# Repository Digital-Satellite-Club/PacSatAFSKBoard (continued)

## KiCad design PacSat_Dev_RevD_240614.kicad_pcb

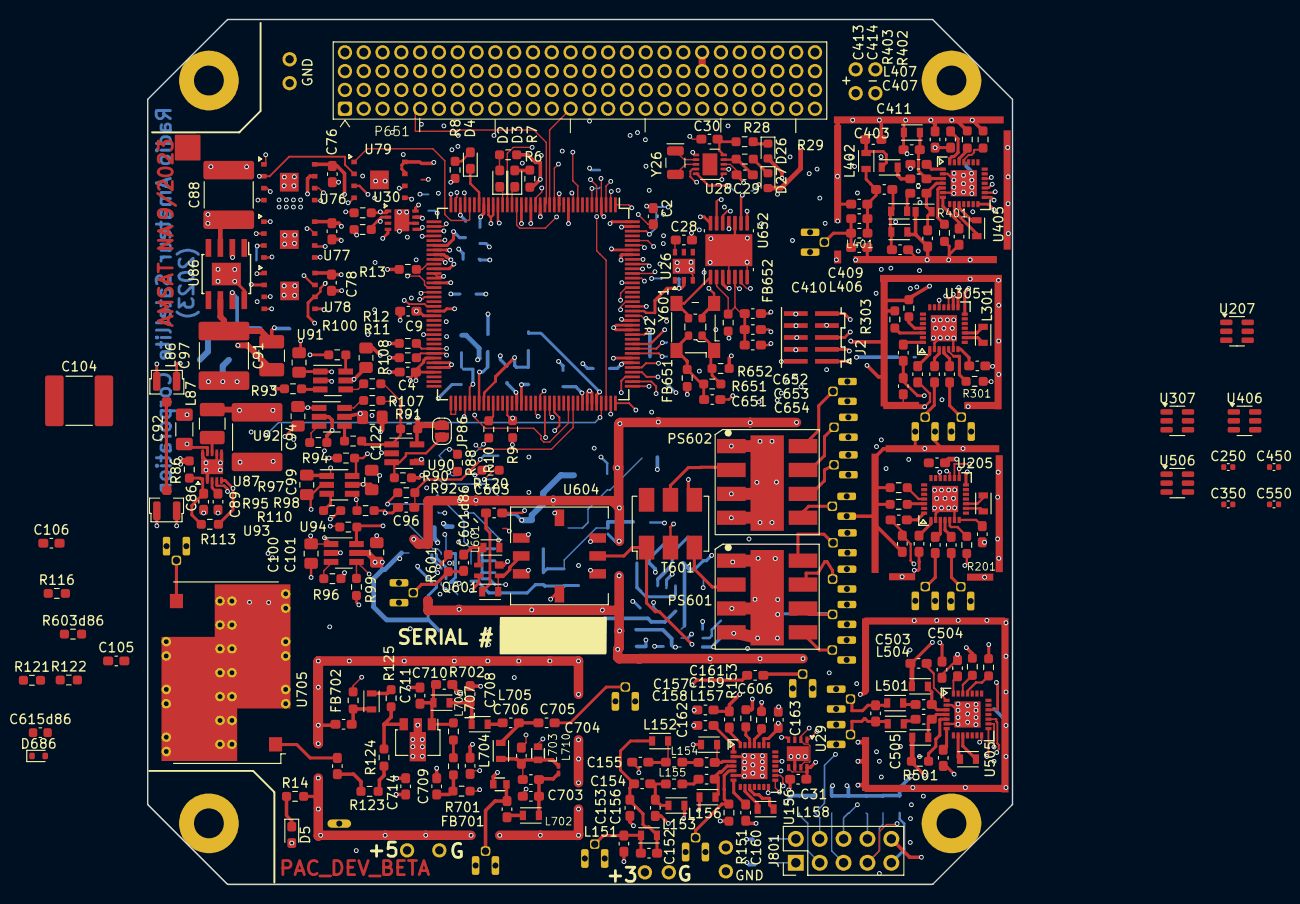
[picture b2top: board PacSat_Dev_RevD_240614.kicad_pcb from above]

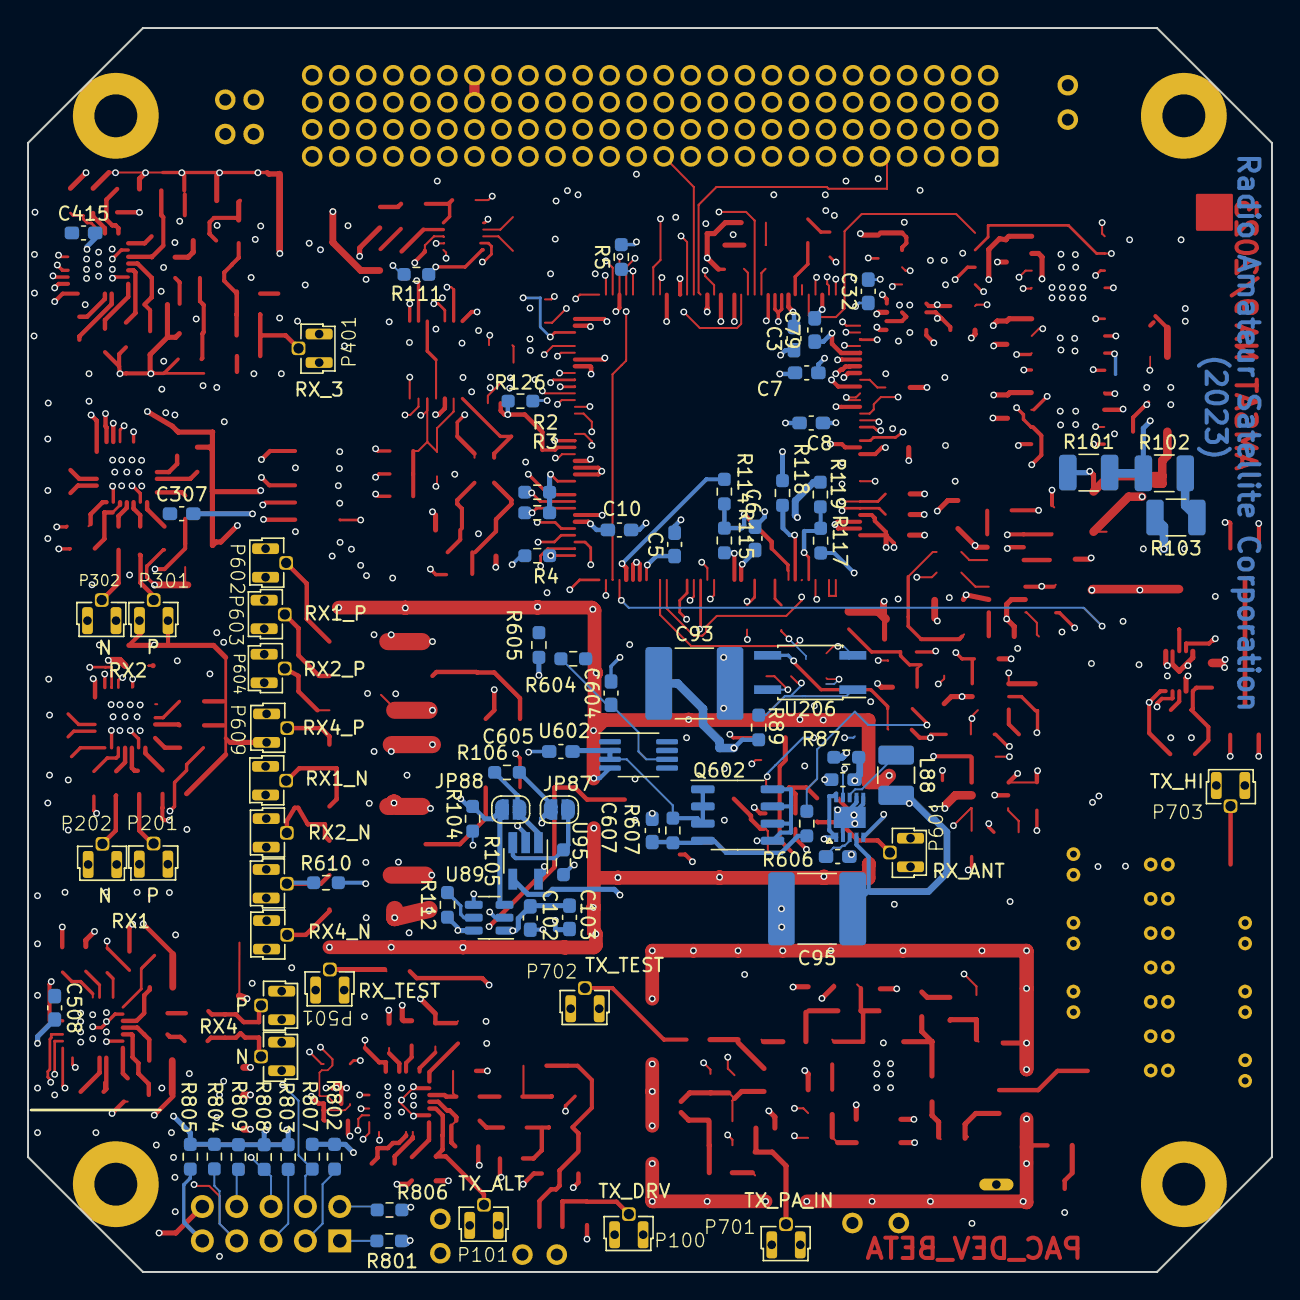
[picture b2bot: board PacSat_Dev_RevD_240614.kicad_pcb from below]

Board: 6 copper layers, 92.0 x 92.0 mm, 354 parts (85 on the bottom side), 245 nets.

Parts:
C2, C3, C4, C5, C6, C7, C8, C9, C10, C31, C32, C76, C77, C78, C79: 100n; C_0603_1608Metric_Pad1.08x0.95mm_HandSolder
C28, C86, C87: 470n; C_0603_1608Metric_Pad1.08x0.95mm_HandSolder
C29, C30: 22u; C_0603_1608Metric_Pad1.08x0.95mm_HandSolder
C88: 16V; C_2220_5750Metric_Pad1.97x5.40mm_HandSolder
C89, C90: 1000p; C_0603_1608Metric_Pad1.08x0.95mm_HandSolder
C91: 22u 10V; C_2220_5750Metric_Pad1.97x5.40mm_HandSolder
C92: 10u; C_1206_3216Metric_Pad1.33x1.80mm_HandSolder
C93: 10u; C_2220_5750Metric_Pad1.97x5.40mm_HandSolder
C94, C95: 22u; C_2220_5750Metric_Pad1.97x5.40mm_HandSolder
C96, C714: 10u; C_0603_1608Metric_Pad1.08x0.95mm_HandSolder
C97, C98, C99, C100, C101, C121, C122, C123: 1u; C_0805_2012Metric_Pad1.18x1.45mm_HandSolder
C102, C103, C159, C160, C163, C203, C204, C207, C303, C304, C307, C411, C412, C415, C504, C505, C508: 10n; C_0603_1608Metric_Pad1.08x0.95mm_HandSolder
C104: 10u 10v; C_2220_5750Metric_Pad1.97x5.40mm_HandSolder
C105, C106, C603, C607: 0.1 u; C_0603_1608Metric_Pad1.08x0.95mm_HandSolder
C151, C152, C153, C402, C704: NS; C_0603_1608Metric_Pad1.08x0.95mm_HandSolder
C154: 5p1; C_0603_1608Metric_Pad1.08x0.95mm_HandSolder
C155: 11p; C_0603_1608Metric_Pad1.08x0.95mm_HandSolder
C156, C406, C702: 5p6; C_0603_1608Metric_Pad1.08x0.95mm_HandSolder
C157, C158, C201, C202, C301, C302, C409, C410, C501, C701, C703: 4p3; C_0603_1608Metric_Pad1.08x0.95mm_HandSolder
C161, C205, C305, C413, C506: 6.8p; C_0603_1608Metric_Pad1.08x0.95mm_HandSolder
C162, C206, C306, C407, C408, C414, C507: 10p; C_0603_1608Metric_Pad1.08x0.95mm_HandSolder
C250, C350, C450, C550: .1u; C_0402_1005Metric
C401, C403: 27p; C_0603_1608Metric_Pad1.08x0.95mm_HandSolder
C404: 12p; C_0603_1608Metric_Pad1.08x0.95mm_HandSolder
C405: 1p; C_0603_1608Metric_Pad1.08x0.95mm_HandSolder
C502, C503: 22p; C_0603_1608Metric_Pad1.08x0.95mm_HandSolder
C601d86: 6p; C_0603_1608Metric_Pad1.08x0.95mm_HandSolder
C604, C605, C707: 1u; C_0603_1608Metric_Pad1.08x0.95mm_HandSolder
C606: 1n; C_0603_1608Metric_Pad1.08x0.95mm_HandSolder
C615d86: 10u; C_0603_1608Metric
C651, C652, C653, C654: 0.1u; C_0603_1608Metric_Pad1.08x0.95mm_HandSolder
C705, C717: 2200p; C_0603_1608Metric_Pad1.08x0.95mm_HandSolder
C706: 18p; C_0603_1608Metric_Pad1.08x0.95mm_HandSolder
C708, C711: 15p; C_0603_1608Metric_Pad1.08x0.95mm_HandSolder
C709, C712: 100p; C_0603_1608Metric_Pad1.08x0.95mm_HandSolder
C710: 56p; C_0603_1608Metric_Pad1.08x0.95mm_HandSolder
D2: RED; LED_0603_1608Metric_Pad1.05x0.95mm_HandSolder
D3: YEL; LED_0603_1608Metric_Pad1.05x0.95mm_HandSolder
D4: GRN; LED_0603_1608Metric_Pad1.05x0.95mm_HandSolder
D5: LED; LED_0603_1608Metric_Pad1.05x0.95mm_HandSolder
D26, D27: RB521CS30L,315; D_0603_1608Metric
D686: BZX58550-C1V8-QX; D_SOD-523
FB651, FB652: FerriteBead_Small; R_0603_1608Metric_Pad0.98x0.95mm_HandSolder
FB701, FB702: 2743019447; R_0603_1608Metric_Pad0.98x0.95mm_HandSolder
H10, H11, H12, H13, H14, H15, H16, H17, H18, H19, H20, H21: Wire_Hole
H101, H102, H103, H104: CUBESAT_MOUNT_HOLE
J2: CONN_02X05; FTSH-105-01-L-DV-K
J801: Conn_02x05_Odd_Even; PinHeader_2x05_P2.54mm_Vertical
JP86, JP87: Disable Watchdog; SolderJumper-2_P1.3mm_Open_RoundedPad1.0x1.5mm
JP88: Disable WD Shutdown; SolderJumper-2_P1.3mm_Open_RoundedPad1.0x1.5mm
L86, L87, L88: 3u3; L_1210_3225Metric_Pad1.42x2.65mm_HandSolder
L151, L158, L201, L301, L408, L505: 0; L_Murata_LQH2MCNxxxx02_2.0x1.6mm
L152, L153: 27n; L_Murata_LQH2MCNxxxx02_2.0x1.6mm
L154, L155: 43n; L_0603_1608Metric_Pad1.05x0.95mm_HandSolder
L156, L157: 100n; L_Murata_LQH2MCNxxxx02_2.0x1.6mm
L401: 30nh; L_0603_1608Metric_Pad1.05x0.95mm_HandSolder
L402, L403, L501, L502, L503, L504: 68n; L_Murata_LQH2MCNxxxx02_2.0x1.6mm
L404, L405: 120n; L_Murata_LQH2MCNxxxx02_2.0x1.6mm
L406, L407: 150n; L_Murata_LQH2MCNxxxx02_2.0x1.6mm
L601: 620nH; L_Murata_LQH2MCNxxxx02_2.0x1.6mm
L602: 120 nH; L_Murata_LQH2MCNxxxx02_2.0x1.6mm
L701: 100n; L_0603
L702: 43n; L_Murata_LQH2MCNxxxx02_2.0x1.6mm
L703: 18n; L_0603
L704: 1n2; L_Murata_LQH2MCNxxxx02_2.0x1.6mm
L705, L706: 5n5; L_Murata_LQH2MCNxxxx02_2.0x1.6mm
L707: 16n6; L_Murata_LQH2MCNxxxx02_2.0x1.6mm
L710: 4n7; L_0201_0603Metric_Pad0.64x0.40mm_HandSolder
P100, P201, P202, P301, P302, P401, P501, P502, P602, P603, P604, P605, P606, P607, P608, P609, P610, P701: U_FL
P101, P601, P702, P703: U_FL
P651: Conn_04x26_Pin; PacSat_Dev_4_26
PS601, PS602: AD4PS+1; CJ725
Q601: SAV-331+; TB-471
Q602: SO-8_3.9x4.9mm_P1.27mm
Q701: ATF05MS004NT1; SOT-89-3
R2, R3, R4, R5, R13: 3k3; R_0603_1608Metric_Pad0.98x0.95mm_HandSolder
R6, R7, R8, R604: 3K; R_0603_1608Metric_Pad0.98x0.95mm_HandSolder
R9, R10, R11, R12: 1k; R_0603_1608Metric_Pad0.98x0.95mm_HandSolder
R14: 2.4K; R_0603_1608Metric_Pad0.98x0.95mm_HandSolder
R28, R29, R30, R31, R104, R111: 4k7; R_0603_1608Metric_Pad0.98x0.95mm_HandSolder
R86, R87, R108, R109, R152, R153, R202, R203, R302, R303, R402, R403, R502, R503: 0R; R_0603_1608Metric_Pad0.98x0.95mm_HandSolder
R88: 20; R_0603_1608Metric_Pad0.98x0.95mm_HandSolder
R89: 2 1/4 W; R_0603_1608Metric_Pad0.98x0.95mm_HandSolder
R90, R91, R105, R106: 10k; R_0603_1608Metric_Pad0.98x0.95mm_HandSolder
R92: 1K; R_0603_1608Metric_Pad0.98x0.95mm_HandSolder
R93, R94, R96: 45k8 1%; R_0603_1608Metric_Pad0.98x0.95mm_HandSolder
R95: 143k 1%; R_0603_1608Metric_Pad0.98x0.95mm_HandSolder
R97, R98, R99, R100, R107, R110, R112, R114, R115, R117, R118, R119, R651, R652, R801, R802, R803, R804, R805, R806, R807, R808, R809: 10K; R_0603_1608Metric_Pad0.98x0.95mm_HandSolder
R101: PLTT1206Z2743BGTS; R_1210_3225Metric_Pad1.30x2.65mm_HandSolder
R102: PLTT1206Z0303BGTS; R_1210_3225Metric_Pad1.30x2.65mm_HandSolder
R103: PLTT1206Z0011BGTS; R_1210_3225Metric_Pad1.30x2.65mm_HandSolder
R113: 3.8K; R_0603_1608Metric_Pad0.98x0.95mm_HandSolder
R116: 440K; R_0603_1608Metric_Pad0.98x0.95mm_HandSolder
R120: 10 1/2 W; R_0603_1608Metric_Pad0.98x0.95mm_HandSolder
R121: 580K; R_0603_1608Metric_Pad0.98x0.95mm_HandSolder
R122: 420K; R_0603_1608Metric_Pad0.98x0.95mm_HandSolder
R123, R124, R702: 0; R_0603_1608Metric_Pad0.98x0.95mm_HandSolder
R125, R151, R201, R301, R401, R501, R610, R701: 50; R_0603_1608Metric_Pad0.98x0.95mm_HandSolder
R126: 20K; R_0603_1608Metric_Pad0.98x0.95mm_HandSolder
R601: 500K; R_0603_1608Metric_Pad0.98x0.95mm_HandSolder
R603d86: 27 1/2 Watt; R_0603_1608Metric_Pad0.98x0.95mm_HandSolder
R605: 2K; R_0603_1608Metric_Pad0.98x0.95mm_HandSolder
R606: 47K; R_0603_1608Metric_Pad0.98x0.95mm_HandSolder
R607: 1MEG; R_0603_1608Metric_Pad0.98x0.95mm_HandSolder
T601: ADT4-1WT+; Mini-Circuits_CD542_H2.84mm
TP1, TP2: U_FL; U_FL SMD
U2: TMS570LS0914PGE; TQFP-144_20x20mm_Pitch0.5mm
U26: DS28E83Q+T; TDFN_T633_2
U28: MAX31331TETB+; TDFN-10-1EP_3x3mm_P0.5mm_EP0.9x2mm
U29, U30: MAX31725MTA+; TDFN_T833_2
U76, U77, U78, U79: MR25H40CDE; MR2xH40_DFN_SmallFlag
U86: TPS7A7001DDA; TI_SO-PowerPAD-8
U87: MAX1556AEBT+; TDFN_T1033_1
U88: MAX1556A; TDFN_T1033_1
U89: TPS22917DBV; SOT-23-6
U90, U95: STWD100NYWY3F; SOT-23-5_HandSoldering
U91, U92, U93, U94: MAX4995ALAUT; SOT-23-6_Handsoldering
U156, U205, U305, U405, U505: AX5043; QFN28
U201: RFShield_OnePiece; RF_SHIELD_BMI_S_201_F_U201
U206: TLP3905; SO-4_4.4x3.6mm_P2.54mm
U207, U307, U406, U506: TPS22929D; SOT-23-6
U301: RFShield_OnePiece; RF_SHIELD_BMI_S_201_F_U301
U401: RFShield_OnePiece; RF_SHIELD_BMI_S_202_F_U401
U501: RFShield_OnePiece; RF_SHIELD_BMI_S_202_F_U501
U602: LT6657AHMS8-2.5; MSOP-8_3x3mm_P0.65mm
U604: RBP-140+; Mini-Circuits_GP731
U652: CDCLVC1106; HTSSOP-14-1EP_4.4x5mm_P0.65mm_EP3.4x5mm_Mask3x3.1mm
U701: RFShield_OnePiece; RF_SHIELD_PAD
U705: SXBP-425+; Mini-Circuits_HF1139_LandPatternPL-230
Y26: 32.768kHz; Crystal_SMD_EuroQuartz_EQ161-2Pin_3.2x1.5mm
Y601: 588S160X2CAT; Oscillator_SMD_CTS_4X5mm
Y602: ECS-TXO-2016-33-160-TR; Oscillator_SMD_ECS_2520MV-xxx-xx-4Pin_2.5x2.0mm

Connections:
+1V2: C3.1, C5.1, C6.1, C9.1, C10.1, C97.1, R118.1, U2.17 (VCC), U2.29 (VCC), U2.45 (VCC), U2.48 (VCC), U2.49 (VCC), U2.57 (VCC), U2.87 (VCC), U2.101 (VCC), U2.114 (VCC), U2.123 (VCC), U2.137 (VCC), U2.143 (VCC), U91.1 (OUT)
+3.3V: C2.1, C4.1, C7.1, C8.1, C32.1, C76.1, C77.1, C78.1, C79.1, C98.1, C605.1, D26.2 (A), FB651.1, FB652.1, H12.1, J2.1, P651.1, P651.9, Q602.1 (S), Q602.2 (S), Q602.3 (S), R2.1, R3.1, R4.1, R6.1, R7.1, R8.1, R11.1, R13.1, R30.1, R31.1, R97.1, R99.1, R100.1, R104.1, R107.1, R110.1, R114.1, R126.1, R607.2, R801.1, R802.1, R803.1, R804.1, R805.1, R806.1, R807.1, R808.1, R809.1, U2.10 (VCCIO), U2.26 (VCCIO), U2.42 (VCCIO), U2.66 (ADREFHI), U2.69 (VCCAD), U2.104 (VCCIO), U2.120 (VCCIO), U2.134 (VCCP), U2.136 (VCCIO), U30.5 (A2), U30.8 (VDD), U76.3 (WP_N), U76.7 (HOLD_N), U76.8 (VDD), U77.3 (WP_N), U77.7 (HOLD_N), U77.8 (VDD), U78.3 (WP_N), U78.7 (HOLD_N), U78.8 (VDD), U79.3 (WP_N), U79.7 (HOLD_N), U79.8 (VDD), U92.1 (OUT), U602.2 (Vin), U602.3 (~SHDN)
+5V: C707.1, C714.1, D5.2 (A), FB702.1, H14.1
-7V BIAS: R92.2, R116.2, R606.1
/RX_1_ax5044/RX1_N: C202.2, P202.1 (In)
/RX_1_ax5044/RX1_P: C201.2, P201.1 (In)
/RX_1_ax5044/RXANT_N: C202.1, U205.4 (ANTN)
/RX_1_ax5044/RXANT_P: C201.1, U205.3 (ANTP)
/RX_2_ax5045/RX2ANT_N: C302.1, U305.4 (ANTN)
/RX_2_ax5045/RX2ANT_P: C301.1, U305.3 (ANTP)
/RX_2_ax5045/RX2A_N: C302.2, P302.1 (In)
/RX_2_ax5045/RX2a_P: C301.2, P301.1 (In)
/RX_3_ax5045/RX3_N: C408.1, C410.1, L406.2, U405.4 (ANTN)
/RX_3_ax5045/RX3_P: C407.1, C409.1, L407.2, U405.3 (ANTP)
/RX_3_ax5045/RX3a_N: C410.2, L405.2
/RX_3_ax5045/RX3a_P: C409.2, L404.2
/RX_3_ax5045/RX3b_N: C404.1, C406.1, L403.1, L405.1
/RX_3_ax5045/RX3b_P: C405.1, L402.2, L404.1
/RX_4_ax5045/RX4ANT_N: C503.1, L504.2, U505.4 (ANTN)
/RX_4_ax5045/RX4ANT_P: C502.1, L503.1, U505.3 (ANTP)
/RX_4_ax5045/RX4a_N: C503.2, L502.2
/RX_4_ax5045/RX4a_P: C502.2, L501.2
/RX_4_ax5045/RX4b_N: C501.2, L502.1, P502.1 (In)
/RX_4_ax5045/RX4b_P: C501.1, L501.1, P501.1 (In)
/Rx_Power_Divider/Port1_N: P605.1 (In), PS601.8 (Port1)
/Rx_Power_Divider/Port1_P: P602.1 (In), PS602.8 (Port1)
/Rx_Power_Divider/Port2_N: P606.1 (In), PS601.7 (Port2)
/Rx_Power_Divider/Port2_P: P603.1 (In), PS602.7 (Port2)
/Rx_Power_Divider/Port3_N: P607.1 (In), PS601.6 (Port3), R610.1
/Rx_Power_Divider/Port3_P: P604.1 (In), PS602.6 (Port3)
/Rx_Power_Divider/Port4_N: P608.1 (In), PS601.5 (Port4)
/Rx_Power_Divider/Port4_P: P609.1 (In), PS602.5 (Port4)
/Rx_Power_Divider/S+: PS602.2 (S1), T601.5 (SB)
/Rx_Power_Divider/S-: PS601.2 (S1), T601.3 (SA)
/TX_ax5043/TCANT_N: C158.1, L156.2, U156.4 (ANTN)
/TX_ax5043/TXANT_P: C157.1, L157.2, U156.3 (ANTP)
/TX_ax5043/TXa_N: C158.2, L155.2
/TX_ax5043/TXa_P: C157.2, L154.2
/TX_ax5043/TXb_N: C154.1, C156.1, L153.1, L155.1
/TX_ax5043/TXb_P: C155.1, L152.2, L154.1
ALERT_SIGNAL: P651.49, U2.15 (N2HET1_22)
ATTACHED: P651.31, U2.106 (N2HET1_8)
AX5043 PWR CTL: R98.1, U2.99 (MIBSPI5SIMO_0), U93.4 (ON)
AX5043_3V3: C31.1, C99.1, C102.2, C103.1, C250.1, C350.1, C450.1, C550.1, U29.5 (A2), U29.8 (VDD), U89.1 (VIN), U93.1 (OUT), U207.4 (VIN), U207.6 (VIN), U307.4 (VIN), U307.6 (VIN), U406.4 (VIN), U406.6 (VIN), U506.4 (VIN), U506.6 (VIN)
AX5043_CLK: J801.8, R809.2, U2.53 (MIBSPI3CLK), U156.15 (CLK), U205.15 (CLK), U305.15 (CLK), U405.15 (CLK), U505.15 (CLK)
AX5043_IRQ: J801.2, R806.2
AX5043_IRQ_RX1: U2.5 (GIOA_1), U205.19 (IRQ)
AX5043_IRQ_RX2: U2.126 (GOIB_0), U305.19 (IRQ)
AX5043_IRQ_RX3: U2.22 (GIOA_7), U405.19 (IRQ)
AX5043_IRQ_RX4: U2.14 (GIOA_5), U505.19 (IRQ)
AX5043_IRQ_TX: U2.142 (GIOB_2), U156.19 (IRQ)
AX5043_MISO: J801.6, R808.2, U2.51 (MIBSPI3SOMI), U156.16 (MISO), U205.16 (MISO), U305.16 (MISO), U405.16 (MISO), U505.16 (MISO)
AX5043_MOSI: J801.4, R807.2, U2.52 (MIBSPI3SIMO), U156.17 (MOSI), U205.17 (MOSI), U305.17 (MOSI), U405.17 (MOSI), U505.17 (MOSI)
AX5043_SEL1: J801.3, R802.2, U2.24 (N2HET1_3), U205.14 (SEL)
AX5043_SEL2: J801.5, R803.2, U2.33 (N2HET1_7), U305.14 (SEL)
AX5043_SEL3: J801.7, R804.2, U2.35 (N2HET1_9), U405.14 (SEL)
AX5043_SEL4: J801.9, R805.2, U2.36 (N2HET1_4), U505.14 (SEL)
AX5043_SEL_TX: J801.1, R801.2, U2.124 (N2HET1_12), U156.14 (SEL)
Alarm XMIT Shutdown: JP88.1, R104.2, U2.118 (N2HET1_10), U28.4 (INTA_N), U89.3 (ON)
CMD_MODE: P651.27, U2.127 (N2HET1_30)
CURRENT_FAULT_U89: U2.73 (AD1IN_2), U2.74 (AD1IN_3)
Clock0: C161.2, C162.1, U652.3 (YO)
Clock1: C205.1, C206.1, U652.14 (Y1)
Clock2: C305.1, C306.1, U652.11 (Y2)
Clock3: C413.1, C414.1, U652.13 (Y3)
Clock4: C506.1, C507.1, U652.6 (Y4)
Clock5: U2.18 (OSCIN), U652.9 (Y5)
Current Fault_1V2: R100.2, U91.6 (FLAG_N)
Current Fault_3V3: R107.2, U92.6 (FLAG_N)
FAULT_N: P651.19, R2.2, U2.117 (nERROR)
FCODE_D0: P651.64, U2.41 (N2HET1_15)
FCODE_D3: P651.60, U2.139 (N2HET1_16)
FCODE_STROBE: P651.56, U2.2 (GIOA_0)
FEED_WATCHDOG: U2.130 (MIBSPI1NCS_1), U90.4 (WDI), U95.4 (WDI)
Find me a CPU gate!: U207.3 (ON), U307.3 (ON), U406.3 (ON), U506.3 (ON)
GIOA_2: P651.15, U2.9 (GIOA_2)
GIOA_6: P651.17, U2.16 (GIOA_6)
GIOB_3: P651.14, U2.1 (GIOB_3)
GND: C2.2, C3.2, C4.2, C5.2, C6.2, C7.2, C8.2, C9.2, C10.2, C28.2, C29.2, C30.2, C31.2, C32.2, C76.2, C77.2, C78.2, C79.2, C86.2, C87.2, C88.2, C89.2, C90.2, C91.2, C92.2, C93.2, C94.2, C95.2, C96.2, C97.2, C98.2, C99.2, C100.2, C101.2, C103.2, C104.2, C105.2, C106.2, C121.2, C122.1, C123.2, C151.2, C153.2, C155.2, C156.2, C159.2, C160.2, C161.1, C163.2, C203.2, C204.1, C205.2, C207.2, C250.2, C303.2, C304.2, C305.2, C307.2, C350.2, C401.2, C403.2, C405.2, C406.2, C407.2, C408.2, C411.2, C412.2, C413.2, C415.2, C450.2, C504.2, C505.2, C506.2, C508.2, C550.2, C603.2, C604.2, C605.2, C607.2, C615d86.2, C651.2, C652.2, C653.2, C654.2, C702.1, C704.2, C707.2, C708.2, C709.2, C710.1, C711.2, C712.2, C714.2, D686.1 (K), H10.1, H11.1, H13.1, H15.1, H16.1, H17.1, H20.1, H21.1, H101.1, H102.1, H103.1, H104.1, J2.3, J2.5, J2.9, J801.10, L153.2, L156.1, L157.1, L403.2, L406.1, L407.1, L503.2, L504.1, L701.1, L703.1, P100.2, P100.3, P101.2, P101.3, P201.2, P201.3, P202.2, P202.3, P301.2, P301.3, P302.2, P302.3, P401.2, P401.3, P501.2, P501.3, P502.2, P502.3, P601.2, P601.3, P602.2, P602.3, P603.2, P603.3, P604.2, P604.3, P605.2, P605.3, P606.2, P606.3, P607.2, P607.3, P608.2, P608.3, P609.2, P609.3, P610.2, P610.3, P651.81, P651.82, P651.84, P701.2, P701.3, P702.2, P702.3, P703.2, P703.3, PS601.1 (GND), PS601.3 (GND), PS601.4 (GND), PS601.9 (PAD), PS602.1 (GND), PS602.3 (GND), PS602.4 (GND), PS602.9 (PAD), Q601.2 (S), Q601.4 (S), Q701.2 (S), R5.2, R9.1, R10.1, R12.1, R14.2, R88.2, R90.2, R93.2, R94.2, R95.2, R96.2, R98.2, R103.2, R105.2, R111.2, R115.2, R117.2, R120.1, R122.2, R151.2, R152.2, R153.2, R201.2, R202.2, R203.2, R301.2, R302.2, R303.2, R401.2, R402.2, R403.2, R501.2, R502.2, R503.2, R601.2, R605.2, R610.2, R652.2, T601.2 (AB), T601.4 (SC), TP1.2, TP1.3, TP2.2, TP2.3, U2.11 (VSS), U2.19 (KELVIN_GND), U2.21 (VSS), U2.27 (VSS), U2.28 (VSS), U2.34 (TEST), U2.43 (VSS), U2.44 (VSS), U2.47 (VSS), U2.50 (VSS), U2.56 (VSS), U2.67 (ADREFLO), U2.68 (VSSAD), U2.88 (VSS), U2.102 (VSS), U2.103 (VSS), U2.115 (VSS), U2.121 (VSS), U2.122 (VSS), U2.135 (VSS), U2.138 (VSS), U2.144 (VSS), U26.0 (EP), U26.3 (GND), U28.1 (GND), U28.8 (DIN), U29.0 (EP), U29.4 (GND), U29.6 (A1), U30.0 (EP), U30.4 (GND), U30.6 (A1), U76.0 (EP), U76.4 (GND), U77.0 (EP), U77.4 (GND), U78.0 (EP), U78.4 (GND), U79.0 (EP), U79.4 (GND), U86.8 (GND), U86.9 (EP), U87.0 (EP), U87.2 (GND), U87.6 (D2), U87.7 (PGND), U87.10 (D1), U88.0 (EP), U88.2 (GND), U88.6 (D2), U88.7 (PGND), U89.2 (GND), U90.2 (GND), U91.2 (GND), U92.2 (GND), U93.2 (GND), U94.2 (GND), U95.2 (GND), U156.0 (GND), U156.2 (GND), U156.6 (GND), U201.1 (Shield), U201.2 (Shield), U201.3 (Shield), U201.4 (Shield), U201.5 (Shield), U205.0 (GND), U205.2 (GND), U205.6 (GND), U206.4, U207.2 (GND), U207.5 (GND), U301.1 (Shield), U301.2 (Shield), U301.3 (Shield), U301.4 (Shield), U301.5 (Shield), U305.0 (GND), U305.2 (GND), U305.6 (GND), U307.2 (GND), U307.5 (GND), U401.1 (Shield), U401.2 (Shield), U401.3 (Shield), U401.4 (Shield), U401.5 (Shield), U405.0 (GND), U405.2 (GND), U405.6 (GND), U406.2 (GND), U406.5 (GND), U501.1 (Shield), U501.2 (Shield), U501.3 (Shield), U501.4 (Shield), U501.5 (Shield), U505.0 (GND), U505.2 (GND), U505.6 (GND), U506.2 (GND), U506.5 (GND), U602.4 (GND), U604.1 (GND), U604.3 (GND), U604.4 (GND), U604.5 (GND), U604.7 (GND), U604.8 (GND), U652.4 (GND), U652.7 (GND), U652.10 (GND), U652.15 (PAD), U701.1 (Shield), U705.2 (GND), U705.3 (GND), U705.4 (GND), U705.5 (GND), U705.6 (GND), U705.7 (GND), Y601.2 (GND), Y602.2 (GND)
GOIB_1: P651.16, U2.133 (GIOB_1)
HW_POWER_OFF_N: P651.23, R113.1, U2.13 (CAN3TX), U87.5 (SHDN_N), U88.5 (SHDN_N)
I2C_SCL: R31.2, U2.3 (MIBSPI3NCS_3), U28.6 (SCL), U29.2 (SCL), U29.7 (A0), U30.2 (SCL)
I2C_SDA: R30.2, U2.4 (MIBSPI3NCS_2), U28.7 (SDA), U29.1 (SDA), U30.1 (SDA), U30.7 (A0)
MRAM_CLK: U2.95 (MIBSPI1CLK), U76.6 (SCK), U77.6 (SCK), U78.6 (SCK), U79.6 (SCK)
MRAM_MISO: U2.94 (MIBSPI1SOMI), U76.2 (SO), U77.2 (SO), U78.2 (SO), U79.2 (SO)
MRAM_MOSI: U2.93 (MIBSPI1SIMO), U76.5 (SI), U77.5 (SI), U78.5 (SI), U79.5 (SI)
MRAM_NCS0: U2.105 (MIBSPI1NCS_0), U76.1 (CS_N)
MRAM_NCS1: U2.55 (MIBSPI3NCS_0), U78.1 (CS_N)
MRAM_NCS2: U2.40 (MIBSPI1NCS_2), U77.1 (CS_N)
MRAM_NCS3: U2.32 (MIBSPI5NCS_0), U79.1 (CS_N)
unnamed: C96.1, R92.1, U206.3
unnamed: C105.1, L601.1, R121.2, R122.1
unnamed: C152.1, C153.1, C154.2, L151.2, L152.1
unnamed: C159.1, U156.1 (VDD_ANA)
unnamed: C160.1, U156.7 (VDD_ANA)
unnamed: C203.1, U205.1 (VDD_ANA)
unnamed: C204.2, U205.7 (VDD_ANA)
unnamed: C303.1, U305.1 (VDD_ANA)
unnamed: C304.1, U305.7 (VDD_ANA)
unnamed: C402.1, C403.1, C404.2, L401.2, L402.1
unnamed: C411.1, U405.1 (VDD_ANA)
unnamed: C412.1, U405.7 (VDD_ANA)
unnamed: C504.1, U505.1 (VDD_ANA)
unnamed: C505.1, U505.7 (VDD_ANA)
unnamed: C603.1, L602.1, R603d86.2
unnamed: C701.2, L702.1
unnamed: C702.2, C703.1, L702.2, L710.1
unnamed: C703.2, C704.1, L703.2, L704.1, L710.2
unnamed: C705.1, C706.2, L704.2
unnamed: C706.1, L705.1
unnamed: C708.1, L705.2, L706.1
unnamed: C709.1, FB701.2, R701.1
unnamed: C712.1, FB702.2, L707.2
unnamed: C717.1, R123.1
unnamed: D2.2 (A), R6.2
unnamed: D2.1 (K), U2.25 (N2HET1_0)
unnamed: D3.2 (A), R7.2
unnamed: D3.1 (K), U2.23 (N2HET1_1)
unnamed: D4.2 (A), R8.2
unnamed: D4.1 (K), U2.30 (N2HET1_2)
unnamed: D5.1 (K), R14.1
unnamed: D26.1 (K), R28.2
unnamed: D27.1 (K), R29.2
unnamed: C106.1, C615d86.1, D686.2 (A), R116.1, R121.1
unnamed: J2.2, U2.108 (TMS)
unnamed: J2.4, U2.112 (TCK)
unnamed: J2.6, U2.111 (TDO)
unnamed: J2.7, U2.113 (RTCK)
unnamed: J2.8, U2.110 (TDI)
unnamed: L707.1, R125.1
unnamed: P101.1 (In), R151.1, U156.5 (ANTP1)
unnamed: C401.1, C402.2, L401.1, P401.1 (In)
unnamed: C601d86.1, P601.1 (In), R601.1
unnamed: C606.1, P610.1 (In)
unnamed: C701.1, L701.2, P701.1 (In)
unnamed: C705.2, P702.1 (In)
unnamed: P703.1 (In), U705.8 (OUT)
unnamed: L602.2, Q601.1 (D), U604.2 (S1)
unnamed: C601d86.2, L601.2, Q601.3 (G)
unnamed: Q602.5 (D), Q602.6 (D), Q602.7 (D), Q602.8 (D), R603d86.1
unnamed: C607.1, Q602.4 (Gate), R606.2, R607.1
unnamed: Q701.3 (D), R124.2, R125.2
unnamed: C710.2, C711.1, L706.2, Q701.1 (G), R702.2
unnamed: R88.1, U206.2
unnamed: R102.2, R103.1
unnamed: R89.1, R120.2, U206.1
unnamed: R123.2, R124.1
unnamed: R701.2, R702.1
unnamed: C606.2, T601.1 (AA), U604.6 (S2)
unnamed: TP1.1 (In), TP2.1 (In)
unnamed: R114.2, R115.1, U2.80 (AD1IN_6)
unnamed: R117.1, R119.2, U2.77 (AD1IN_12)
unnamed: R118.2, U2.79 (AD1IN_13)
unnamed: R5.1, U2.6 (N2HET1_11)
unnamed: R13.2, U2.46 (nPORRST)
unnamed: R4.2, U2.109 (nTRST)
unnamed: C28.1, U26.6 (CEXT)
unnamed: R111.1, U28.5 (INTB_N)
unnamed: C30.1, R28.1, U28.10 (VCC)
unnamed: C29.1, R29.1, U28.9 (Vbat)
unnamed: U28.3 (X1), Y26.2
unnamed: U28.2 (X2), Y26.1
unnamed: R101.2, R102.1, U86.7 (FB)
unnamed: C91.1, C104.1, L86.1, R101.1, U86.6 (OUT)
unnamed: C86.1, R86.2, R113.2, U87.1 (IN)
unnamed: L87.1, U87.8 (LX)
unnamed: C89.1, U87.3 (SS)
unnamed: C87.1, R87.2, U88.1 (IN), U88.10 (D1)
unnamed: L88.1, U88.8 (LX)
unnamed: C90.1, U88.3 (SS)
unnamed: C102.1, U89.4 (CT)
unnamed: R112.2, U89.5 (QOD)
unnamed: JP86.2, R90.1, U90.3 (EN_N)
unnamed: R108.1, U91.4 (ON)
unnamed: R93.1, U91.3 (SETI)
unnamed: R109.1, U92.4 (ON)
unnamed: R94.1, U92.3 (SETI)
unnamed: R95.1, U93.3 (SETI)
unnamed: R96.1, U94.3 (SETI)
unnamed: JP87.2, R105.1, U95.3 (EN_N)
unnamed: JP88.2, R106.2, U95.1 (WDO_N)
unnamed: C162.2, U156.28 (CLK16P)
unnamed: R152.1, U156.25 (GPADC1)
unnamed: R153.1, U156.26 (GPADC2)
unnamed: L158.2, U156.10 (L1)
unnamed: L158.1, U156.9 (L2)
unnamed: C163.1, R112.1, U89.6 (VOUT), U156.23 (VDD_IO)
unnamed: R201.1, U205.5 (ANTP1)
unnamed: C206.2, U205.28 (CLK16P)
unnamed: R203.1, U205.25 (GPADC1)
unnamed: R202.1, U205.26 (GPADC2)
unnamed: L201.2, U205.10 (L1)
unnamed: L201.1, U205.9 (L2)
unnamed: C207.1, U205.23 (VDD_IO), U207.1 (VOUT)
unnamed: R301.1, U305.5 (ANTP1)
unnamed: C306.2, U305.28 (CLK16P)
unnamed: R302.1, U305.25 (GPADC1)
unnamed: R303.1, U305.26 (GPADC2)
unnamed: L301.2, U305.10 (L1)
unnamed: L301.1, U305.9 (L2)
unnamed: C307.1, U305.23 (VDD_IO), U307.1 (VOUT)
unnamed: R401.1, U405.5 (ANTP1)
unnamed: C414.2, U405.28 (CLK16P)
unnamed: R402.1, U405.25 (GPADC1)
unnamed: R403.1, U405.26 (GPADC2)
unnamed: L408.2, U405.10 (L1)
unnamed: L408.1, U405.9 (L2)
unnamed: C415.1, U405.23 (VDD_IO), U406.1 (VOUT)
unnamed: R501.1, U505.5 (ANTP1)
unnamed: C507.2, U505.28 (CLK16P)
unnamed: R502.1, U505.25 (GPADC1)
unnamed: R503.1, U505.26 (GPADC2)
unnamed: L505.2, U505.10 (L1)
unnamed: L505.1, U505.9 (L2)
unnamed: C508.1, U505.23 (VDD_IO), U506.1 (VOUT)
unnamed: C604.1, R604.1, U602.6 (OUT)
unnamed: C652.1, C653.1, C654.1, FB652.2, U652.2 (1G), U652.5 (Vdd), U652.8 (Vdd), U652.12 (Vdd)
unnamed: U652.1 (CLKIN), Y601.3 (OUT), Y602.3 (OUT)
unnamed: C717.2, U705.1 (IN)
unnamed: R651.2, R652.1, Y601.1 (VC), Y602.1 (Tri-State)
unnamed: C651.1, FB651.2, R651.1, Y601.4 (VDD), Y602.4 (VDD)
ONEWIRE: R126.2, U2.125 (N2HET1_14), U26.2 (IO)
Optional Reset Push Button: J2.10, R3.2, U2.116 (nRST)
PA PWR CTL: R99.2, U2.98 (MIBSPI5SOMI_0), U94.4 (ON)
PB_ENABLE: P651.45, U2.107 (N2HET1_28)
PWR_FLAG_AX5043: R97.2, U2.61 (AD1IN_7), U93.6 (FLAG_N)
PWR_FLAG_SSPA: R110.2, U2.76 (AD1IN_4), U94.6 (FLAG_N)
REG_1V2: C95.1, C121.1, L88.2, U88.4 (OUT), U91.5 (IN)
REG_3V3: C94.1, C122.2, C123.1, JP86.1, JP87.1, L87.2, R91.1, R106.1, U87.4 (OUT), U90.5 (VCC), U92.5 (IN), U93.5 (IN), U95.5 (VCC)
REG_5.0V: C93.1, C101.1, L86.2, R86.1, R87.1, R89.2, R119.1, U88.9 (INP), U94.5 (IN)
SSPA_VCC: C100.1, U94.1 (OUT)
TX_OUT_DRV: C151.1, C152.2, L151.1, P100.1 (In)
UART_CTS: P651.100, U2.91 (N2HET1_24)
UART_RTS: P651.96, U2.92 (N2HET1_26)
UART_RX1: P651.92, U2.38 (N2HET1_6)
UART_RX2: P651.36, U2.131 (LINRX)
UART_TX1: P651.88, U2.39 (N2HET1_13)
UART_TX2: P651.32, U2.132 (LINTX)
USB_Suspend_Low: P651.104, U2.140 (N2HET1_18)
VER_BIT0: P651.39, R12.2, U2.64 (AD1IN_20)
VER_BIT1: P651.35, R11.2, U2.65 (AD1IN_21)
VER_BIT2: R10.2, U2.82 (AD1IN_14)
VER_BIT3: P651.43, R9.2, U2.85 (AD1IN_15)
VSYS: C88.1, C92.1, D27.2 (A), H18.1, H19.1, P651.79, P651.80, U86.2 (EN), U86.3 (IN), U87.9 (INP)
WDO_N: R91.2, R108.2, R109.2, U90.1 (WDO_N)

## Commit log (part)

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2025-07-23 Move over Bob's PacSat Rev D board
2025-07-23 Lots of cleanups to fix numerous issues
2025-07-24 Add some missing footprints
    I was able to pull them from the PCB.
2025-07-24 Rename the project
2025-07-25 Add one more note about capacitors
2025-07-25 Start ripping things apart
2025-07-25 More hacking on things
2025-07-25 Work on power
2025-07-26 Finish up most of the ax5043 routing
2025-07-26 Do a lot of routing work
    RX input is done, 5043s are done, power is done.
2025-07-26 Switch regulators to ones with power good
    Tie that into reset.
2025-07-27 More cleanup, finish hooking up power supply controls
2025-07-27 Wire in clocks, more cleanups, wire in MRAM
2025-07-27 More cleanups and notes of things to handle
2025-07-28 Add a CPU thermsistor
2025-07-28 Simulate RF input filter and adjust values
2025-07-28 Add resistors to the JTAG interface
    They are supposed to be there.
2025-07-28 Clean up tracks on the board
2025-07-28 Added a coplaner connection between the RX filter and hybrid
    Just playing around to see hard hard it is to draw curved traces and set
    up a coplaner.
2025-07-29 Do coplanar for the connections to the AX5043
2025-07-29 Lots of notes and things about various items
2025-07-29 Add shields around AX5043s, replace UFL connectors
2025-07-29 Add a bunch of decoupling capacitors
2025-07-29 Size up some power lines
2025-07-30 Set orientaion of the shields, add bleed off inductor to TX
2025-07-30 Update SPI clock with simulation
    Simulated the SPI clocks, updated resistor values based on findings.
2025-07-30 Rework the AX5043 RX side to a different balun
    It's cheaper (though not smaller) and fits inside the shield.
2025-07-30 Add a shield on the RF input section
2025-07-30 Add shield for the TX PA section
2025-07-30 Notes cleanup
2025-07-30 Add impedance calculation for the QPL9547
2025-07-30 Rounded some corners in the RF section
2025-07-31 Replace the 1.2V current limited with a MP5073
    The MAX4495 part that was there wasn't rated for 1.2V.
2025-07-31 Remove the Current Fault for 1.2 and 3.3V
    The didn't go anywhere.
2025-07-31 Lots of cleanups around the RF shield
2025-07-31 Run power good on 1.2V current chip, add pinout document
2025-07-31 Clean up some notes
2025-07-31 Create hierarchical sheets for the AX5043s
2025-07-31 Re-annotate all parts
    And get rid of the per-sheet annotation remarks.
2025-08-01 Rework the LNA impedance matching
2025-08-01 More cleanup around the LNA
    Had the C/L order on the output impedance match wrong.
    Change the double 3pf caps to a 1.5pf, I think a suitable one can be
    found.
2025-08-01 Improve the LNA layout some more
2025-08-01 One more little tweak in the LNA
2025-08-01 More work on the LNA
    Rework the filter a bit, rework the layout.
2025-08-01 More minor cleanups in the LNA section
2025-08-01 More shield work
2025-08-01 Rework the LNA input filter
    Some more :(
2025-08-02 Lots of work on the documentation
2025-08-02 Fix some markdown issues in the processor pin document
2025-08-02 More notes and minor changes
2025-08-03 Add power measurement on TX
    Add chips for forward and reverse power.
2025-08-03 More work on the notes
2025-08-04 More notes, added a pullup on LNA_ENABLE_N
2025-08-04 Rework AX5043 and PA power enables
    The way they were wasn't going to work, make the enables active high.
2025-08-04 Rework the LNA enable line
    Don't connect +5V through a pullup to a GPIO. That's not in spec
    for the GPIO lines.
2025-08-04 Notes cleanups, replace LNA enable MOSFET with BSS138
2025-08-04 Replace the AX5043 MOSFETs again
    A little wider VTgs and lower on resistance.
2025-08-04 Fix an issue in the processor pins table
2025-08-04 Change TX bleed off inductor to bigger one
    100nH really isn't big enough.
2025-08-04 Move the UFL connectors closer to the traces
    Create less of a stub.
2025-08-04 Check over notes and some component values
    Fix a wrong capacitor in one spot, set Q and voltage as necessary.
2025-08-04 Adjust the TX output impedance match some more
2025-08-05 Minor text adjustment
2025-08-05 Minor notes cleanups
2025-08-05 Fix values of a lot of parts
    Make them standard, 4.1p instead of 4p1, etc.
    Add a tag to a couple of ICs that didn't have a pin 1 indicator on the
    board.
2025-08-06 Minor adjustments to values and impedance match simulation
2025-08-06 Set load impedance properly in the impedance match simulation
2025-08-06 Add some notes, fix the diode footprints on the RTC
2025-08-06 More notes on the RTC
2025-08-06 Push previous updates to the PCB
2025-08-06 Add ferrite beads to the AX5043s' power inputs
2025-08-08 Move the RTC and rework it a bit
2025-08-08 Remove the HW_SENSE line
    It's not necessary in our setup.
2025-08-08 Added a connector for the UART1 interface
2025-08-08 More work on various things
2025-08-08 Change a resistor, add a bunch of ground vias
2025-08-08 Rework the MRAM device interface
    Use pull ups instead of connecting pins right to +3.3V.
2025-08-08 Add a second CAN bus interface
    Redundancy...
2025-08-10 Add info on automotive qualified components
2025-08-10 Did a track cleanup
2025-08-12 Add active/standby configuration for the board
2025-08-12 Start working on active/standby handling
2025-08-13 Make some room for another SMA for transmit
2025-08-13 Added active/standy support for TX RF and did docs
2025-08-13 Add missing sheets, move active standby to its own hierarchy
2025-08-13 Added some missed notes
2025-08-13 Moved ACTIVE\_N to a normal GPIO so it can be interrupt driven
2025-08-13 More information and notes
2025-08-13 Add an RF loopback test
2025-08-13 Add some ground vias
    Need to have them scattered about.
2025-08-14 Increase some power track widths
    Make sure they are fat enough to carry the necessary power.
2025-08-14 Change RF connectors to U.FL
    I'll solder a U.FL to SMA connector for testing.
2025-08-14 Change a transistor to a SOT-523
    Save some space
2025-08-15 Rework passives around the CPU to be 0402
2025-08-15 Change clock and MRAM passives to 0402
2025-08-15 Convert the LNA and PA portions to 0402
    Where appropriate
2025-08-15 Change appropriate passives to 0402 on the receive AX5043s
2025-08-15 Add a current limiter for on-board +5V devices
2025-08-15 Add some more notes about automotive ratings
2025-08-15 Try to get tables in the notes working
2025-08-16 Fixed DC bias issue on the output impedance filter of the LNA
2025-08-16 Replace the output filter with a discrete one
    The part chosen for the output filter didn't have very good ratings with
    respect to being shaken and nothing on thermal cycles. Also, it only
    had 30dB of output filtering. Replace with a discrete filter.
2025-08-16 Change 3.3V power convert to a TPS7A52-Q1
    It's AEC rated.
2025-08-18 Yet more updates on impedance matching
2025-08-20 More note changes
2025-08-20 Remove the UART connections from the PC104
2025-08-22 Make a little more space around the MRAM
    Change the orientation of some resistors.
2025-08-23 More work on components
2025-08-23 More work on simulation and component choice
2025-08-24 Move the RF splitter over
    Make some room in case we move to a discrete filter.
2025-08-25 Replace the LNA output filter with discretes
    These take up some more room, but are much cheaper and perform
    quite a bit better.
2025-08-25 Update some inductor values
    Fix some small issues.
    Add a 0 ohm resistor between the LNA output and the filter.
2025-08-25 Move things around to neaten them
2025-08-25 Add the LNA output filter simulation
2025-08-26 Track cleanup
2025-08-27 Massive rework of filtering and inductors
    Now that I know how inductors really work.
2025-08-27 Take into account capacitance of inductors
2025-08-27 More simulation cleanups
2025-08-27 Track and doc cleanups
2025-08-27 Reset origin to 0,0 to make the board easier to set up
2025-08-28 More work converting to the CubeSat Kit Bus
2025-08-28 Have the BOM file fixer output xls, not csv
    The omega symbol gets translated properly from xls.
2025-08-28 Add some missing footprints
2025-08-28 Misses a save, this goes with previous changes
2025-08-28 Move the JTAG connector
    Don't put it in the slot, that might be used to run cables or
    otherwise make the connector inaccessible.
2025-08-28 Track and via cleanup
2025-08-28 Minor updates
2025-08-29 Fix POWER_ENABLE to disable 3.3V
2025-08-29 Add an UMBILICAL_ATTACHED signal from the PC104
    Allow the board to know if it is in the launch vehicle. Will
    hardware inhibit transmit.
2025-08-29 Make room for moving the mounting holed for the 92x92 board
    Leave areas free so they can be moved easily.
2025-08-30 More prettying up, add some missing footprints
2025-09-01 A bunch of work on component selections
    And little fixups for things I found.
2025-09-01 More minor part number updates
2025-09-01 Renumber shields and PC104 sockets
    Separate out shields into their own designator category.
    Make the PC104 sockets J1 and J2 to make it easier to move to other
    boards.
2025-09-01 Remove everything except the CSKB base parts
2025-09-02 More minor cleanups
    Tune the CAN bus lines.
    Clean up some tracks.
2025-09-02 Convert MRAM parts into SIOC packages
    More reliability with thermal cycling.
2025-09-02 Move to two smaller shields for the TX section
2025-09-02 More minor cleanups, add vias for shields
2025-09-02 Replace the 1.2V regulator with a non-module
    It's automotive rated and better for heat cycling.
2025-09-03 Add antenna control connector
2025-09-03 Add Power System Adapter function to the board
2025-09-04 More little cleanups, allow 3.3V to power 1.2V
2025-09-04 Make room to allow 3.3V to power 1.2V
    A trace can be run easily now.
2025-09-04 Added an option to power 1.2V from 3.3V or 5V
2025-09-04 Missed a BOM setting on a part
2025-09-05 Add docs for the 1.2V input config
2025-09-06 Update the location and add a CSKB light connection
    Move UMBILICAL_ATTACHED to the CSKB lite area, and add a SAFE\_MODE
    pin to trigger the processor from another board to go into safe mode.
2025-09-06 Add connections to I2C on the PC104
2025-09-09 Lots of little cleanups
2025-09-09 Add the missing adapter schematics
2025-09-09 Convert back to the CSKB setup
2025-09-09 Add more infromation about configuration
    And add a zero-ohm resistor for bypassing the power off pin.
2025-09-09 Some track cleanups and notes
2025-09-09 Rename BOM and POS fixup files
    The apply to any board manufacturer.
2025-09-09 Add some missing BOM parts
2025-09-15 Get the CSKB board ready for build
    Change some DNPs, neaten things up a little on the schematic.
2025-09-16 Add a pullup to the LMK1C1106A (clock dist) enable
    The spec sheet says to use a pullup, but it was directly connected
    to +3.3V.
2025-09-18 Fix some processor pins that were wrong
2025-09-18 Fix some processor pin comments
2025-09-26 Remove unused schematic file
2025-10-12 Fix a bug in the RF switch circuitry
    The board bypass circuitry had an error, the board1 in and antenna
    connections were flipped on the switch. Put them in the right place.
2025-12-31 Add more board info and notes
    Working on the boards...
2025-12-31 More info on boards, fix simulation to match the board
2026-01-03 More board tweaks
2026-01-05 Add some more board info
2026-01-20 Work on the PA output filter to get the match right
2026-01-20 More matching changes
